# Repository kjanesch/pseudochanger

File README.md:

pseudochanger
=============
A project that aims to add an auxiliary input to head units that use the Panasonic variant of the Alpine MBus protocol.

Alpine MBus is a bidirectional one-wire serial interface used for communication between audio head units and peripherals like CD players, CD changers, and tape decks. A period for each bit is 3 ms, and low/high bits are indicated by how long the line is held low. Low for the first 600us indicates a 1, low for 1800 us indicates a 0. Data is a multiple of four bits, and a four-bit check follows the packet, an XOR of all the other 4-bit chunks.

The Panasonic variant uses different ping and ACK codes, sends some data at different times, and does what looks like type detection by sending out a cycle of codes. The included library reflects these differences.

This project was developed specifically for the 2002 Subaru WRX head unit, model CQ-EF7260A, and should work with other Panasonic head units that have the same 16-pin connector on the back, as also found in some Mazdas and Hondas.

This project contains:
 - Arduino MBusPanasonic library
   - Timing-driven bus interface
   - Sends static timestamp of Disc 1, Track 1, Time A:0A to indicate aux input 
 - Example implementation (pseudochanger)
   - Uses the Teensy branch of [finsprings/arduinaap](https://github.com/finsprings/arduinaap/tree/teensy) for the iPod Accessory Protocol interface.
 - Circuit and PCB diagrams
   - V1 is the handmade, free-handed version
   - V2 is the (incomplete) PCB of V1 with minor tweaks
   - V2.5 is a completely respun, integrated design
     - Built-in Atmega 32U4 (or 16U4 depending on code space needs)
     - Onboard switching regulator to generate 5V supply from +12V and accessory on/off
     - Smaller (0805/0603) SMT components
     - Ethernet jack for iPod connector
     - Op-amp based switch to make it solid state

TODO: 
 - Library:
   - Interrupt-driven approach to receiving and sending MBus data
   - Integrated polling routine to extract button presses
   - Fix issues with generating timestamps
   - Add a short example that doesn't keep state, switch between inputs, or control iPods (fewer I/Os, less setup, smaller code, no dependencies)
 - Implementation: 
   - Sort out why iPod interface doesn't work (Hardware? Software?)
 - EAGLE files:
   - Finish V2.5 PCB and BOM, construct boards IRL and test

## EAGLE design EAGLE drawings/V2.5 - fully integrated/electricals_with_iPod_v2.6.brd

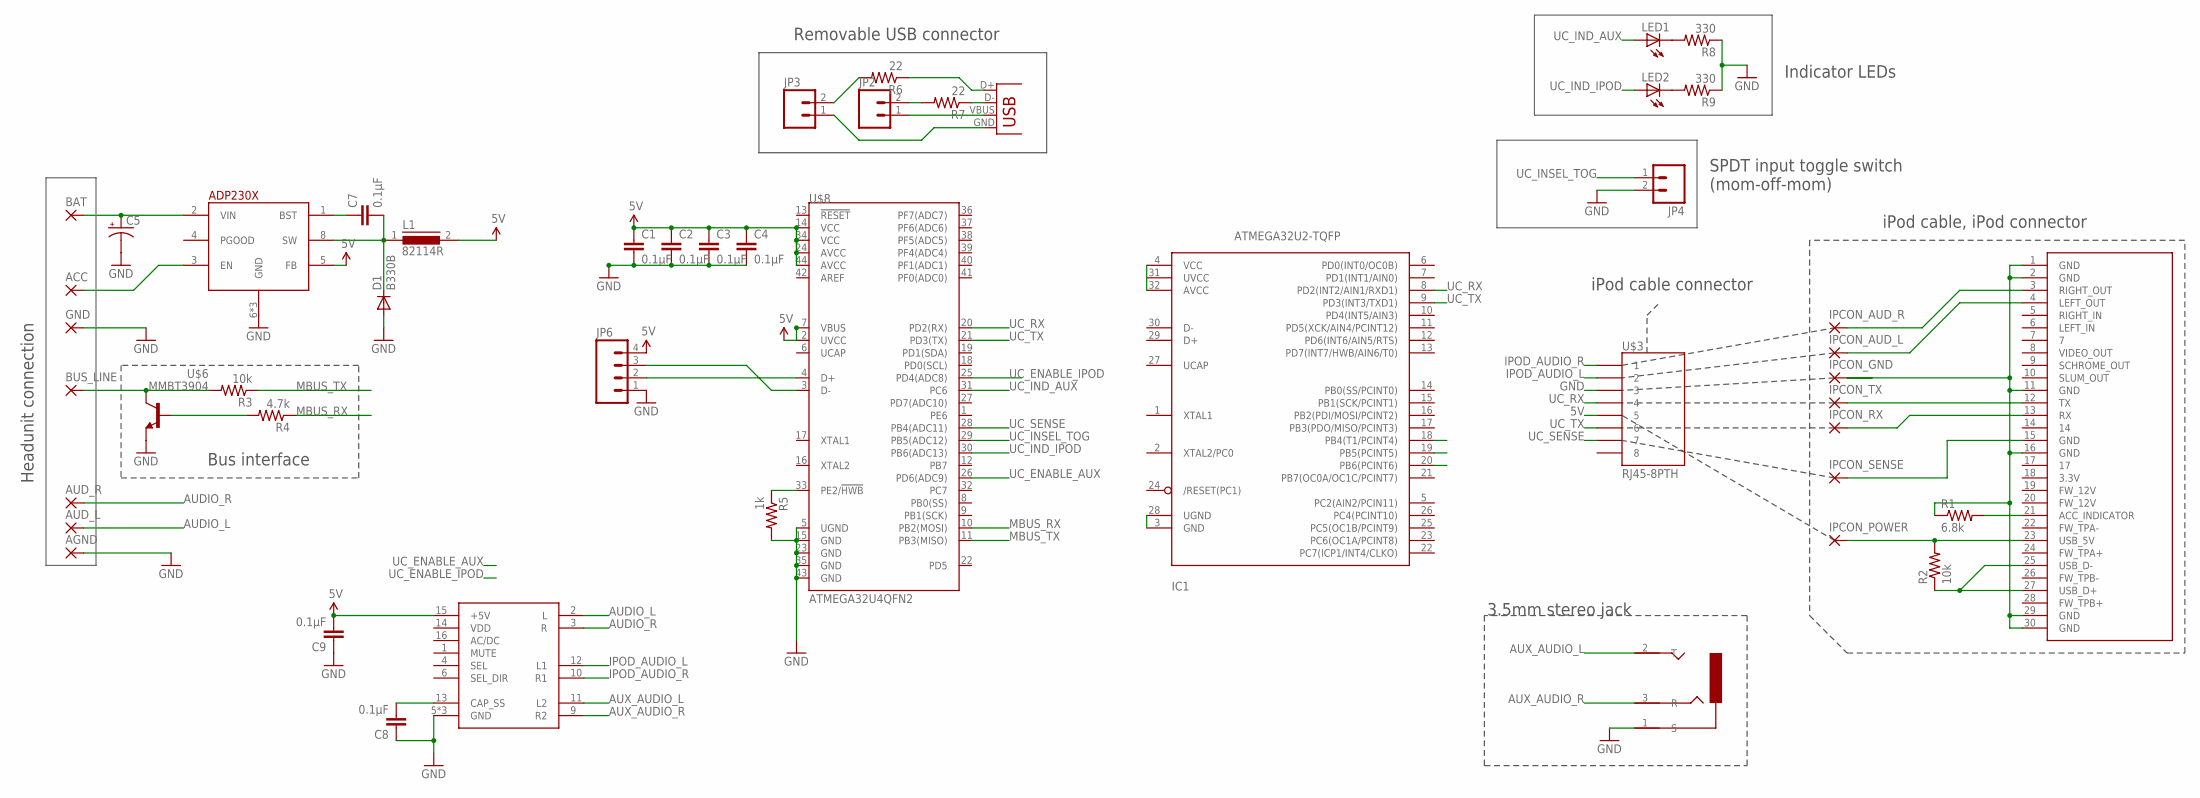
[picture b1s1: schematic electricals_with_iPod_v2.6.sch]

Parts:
ACC: 1,6/0,9
AGND: 1,6/0,9
AUD_L: 1,6/0,9
AUD_R: 1,6/0,9
BAT: 2,54/1,1
BUS_LINE: 1,6/0,9
C1, C2, C3, C4, C7, C8, C9: 0.1µF; 0603-CAP
C5: CAP_POLPTH2; CPOL-RADIAL-10UF-25V
D1: B330B; SMA-DIODE_ALT
GND: 2,54/1,1
IC1: ATMEGA32U2-TQFP; TQFP32-08
IPCON_AUD_L: 1,6/0,9
IPCON_AUD_R: 1,6/0,9
IPCON_GND: 1,6/0,9
IPCON_POWER: 1,6/0,9
IPCON_RX: 1,6/0,9
IPCON_SENSE: 1,6/0,9
IPCON_TX: 1,6/0,9
JP1: USBSMD; USB-MINIB
JP2, JP3: M02POGO_PIN_HOLES_ONLY; 1X02_PP_HOLES_ONLY
JP4: M02LOCK; 1X02_LOCK
JP6: M04PTH; 1X04
L1: 82114R
LED1, LED2: LED0603; LED-0603
R1: 6.8k; 0603-RES
R2, R3: 10k; 0603-RES
R4: 4.7k; 0603-RES
R5: 1k; 0603-RES
R6, R7: 22; 0603-RES
R8, R9: 330; 0603-RES
U$1: IPOD_CONNECTOR_MALE; IPOD_MALE_CONNECTOR
U$3: RJ45-8PTH; RJ45-8
U$5: ADP230X; SO8-THERM
U$6: MMBT3904; SOT23-3
U$7: STEREO_JACK_SJ1-353XNG3NG; 3.5MM_SJ1-353XNG
U$8: ATMEGA32U4QFN2; SPARKFUN-DIGITALIC_QFN-44-NOPAD
U$11: ISL54405IRTZ; QFN-16

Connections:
5V: C1.1, C2.1, C3.1, C4.1, C9.2, JP6.4, L1.2, U$3.5, U$5.5 (FB), U$8.2 (UVCC), U$8.7 (VBUS), U$8.14 (VCC), U$8.24 (AVCC), U$8.34 (VCC), U$8.44 (AVCC), U$11.15 (+5V)
AUDIO_L: AUD_L.1, U$11.2 (L)
AUDIO_R: AUD_R.1, U$11.3 (R)
AUX_AUDIO_L: U$7.2 (T), U$11.11 (L2)
AUX_AUDIO_R: U$7.3 (R), U$11.9 (R2)
GND: AGND.1, C1.2, C2.2, C3.2, C4.2, C5.2 (-), C8.1, C9.1, D1.A, GND.1, JP4.2, JP6.1, R5.2, R8.1, R9.1, U$3.3, U$5.6 (GND), U$5.7 (GND), U$5.PAD (GND), U$6.2 (E), U$7.1 (S), U$8.5 (UGND), U$8.15 (GND), U$8.23 (GND), U$8.35 (GND), U$8.43 (GND), U$11.5 (GND), U$11.7 (GND), U$11.8 (GND)
IPOD_AUDIO_L: U$3.2, U$11.12 (L1)
IPOD_AUDIO_R: U$3.1, U$11.10 (R1)
IP_GND: IPCON_GND.1, R1.1, U$1.1 (GND), U$1.2 (GND), U$1.11 (GND), U$1.16 (GND), U$1.29 (GND), U$1.30 (GND)
MBUS_RX: R4.1, U$8.10 (PB2(MOSI))
MBUS_TX: R3.1, U$8.11 (PB3(MISO))
unnamed: ACC.1, U$5.3 (EN)
unnamed: BAT.1, C5.1 (+), U$5.2 (VIN)
unnamed: C7.2, D1.C, L1.1, U$5.8 (SW)
unnamed: IPCON_POWER.1, R2.2, U$1.23 (USB_5V)
unnamed: C7.1, U$5.1 (BST)
unnamed: IPCON_SENSE.1, U$1.15 (GND)
unnamed: IPCON_RX.1, U$1.13 (RX)
unnamed: IPCON_TX.1, U$1.12 (TX)
unnamed: IPCON_AUD_R.1, U$1.3 (RIGHT_OUT)
unnamed: IPCON_AUD_L.1, U$1.4 (LEFT_OUT)
unnamed: R2.1, U$1.25 (USB_D-), U$1.27 (USB_D+)
unnamed: C8.2, U$11.13 (CAP_SS)
unnamed: R1.2, U$1.21 (ACC_INDICATOR)
unnamed: R5.1, U$8.33 (PE2/!HWB)
unnamed: LED1.C, R8.2
unnamed: LED2.C, R9.2
unnamed: IC1.3 (GND), IC1.28 (UGND)
unnamed: IC1.4 (VCC), IC1.32 (AVCC)
unnamed: BUS_LINE.1, R3.2, U$6.3 (C)
unnamed: R4.2, U$6.1 (B)
unnamed: JP1.D+, R6.1
unnamed: JP1.D-, R7.1
UC_ENABLE_AUX: U$8.26 (PD6(ADC9))
UC_ENABLE_IPOD: U$8.25 (PD4(ADC8))
UC_IND_AUX: LED1.A, U$8.31 (PC6)
UC_IND_IPOD: LED2.A, U$8.30 (PB6(ADC13))
UC_INSEL_TOG: JP4.1, U$8.29 (PB5(ADC12))
UC_RX: IC1.8 (PD2(INT2/AIN1/RXD1)), U$3.4, U$8.20 (PD2(RX))
UC_SENSE: U$3.7, U$8.28 (PB4(ADC11))
UC_TX: IC1.9 (PD3(INT3/TXD1)), U$3.6, U$8.21 (PD3(TX))
USB_BOB_D+: JP3.2, R6.2
USB_BOB_D-: JP2.2, R7.2
USB_BOB_GND: JP1.GND, JP3.1
USB_BOB_VBUS: JP1.VBUS, JP2.1
USB_D+: JP6.2, U$8.4 (D+)
USB_D-: JP6.3, U$8.3 (D-)

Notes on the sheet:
Bus interface
SPDT input toggle switch (mom-off-mom)
3.5mm stereo jack
Indicator LEDs
iPod cable, iPod connector
iPod cable connector
Headunit connection
Removable USB connector

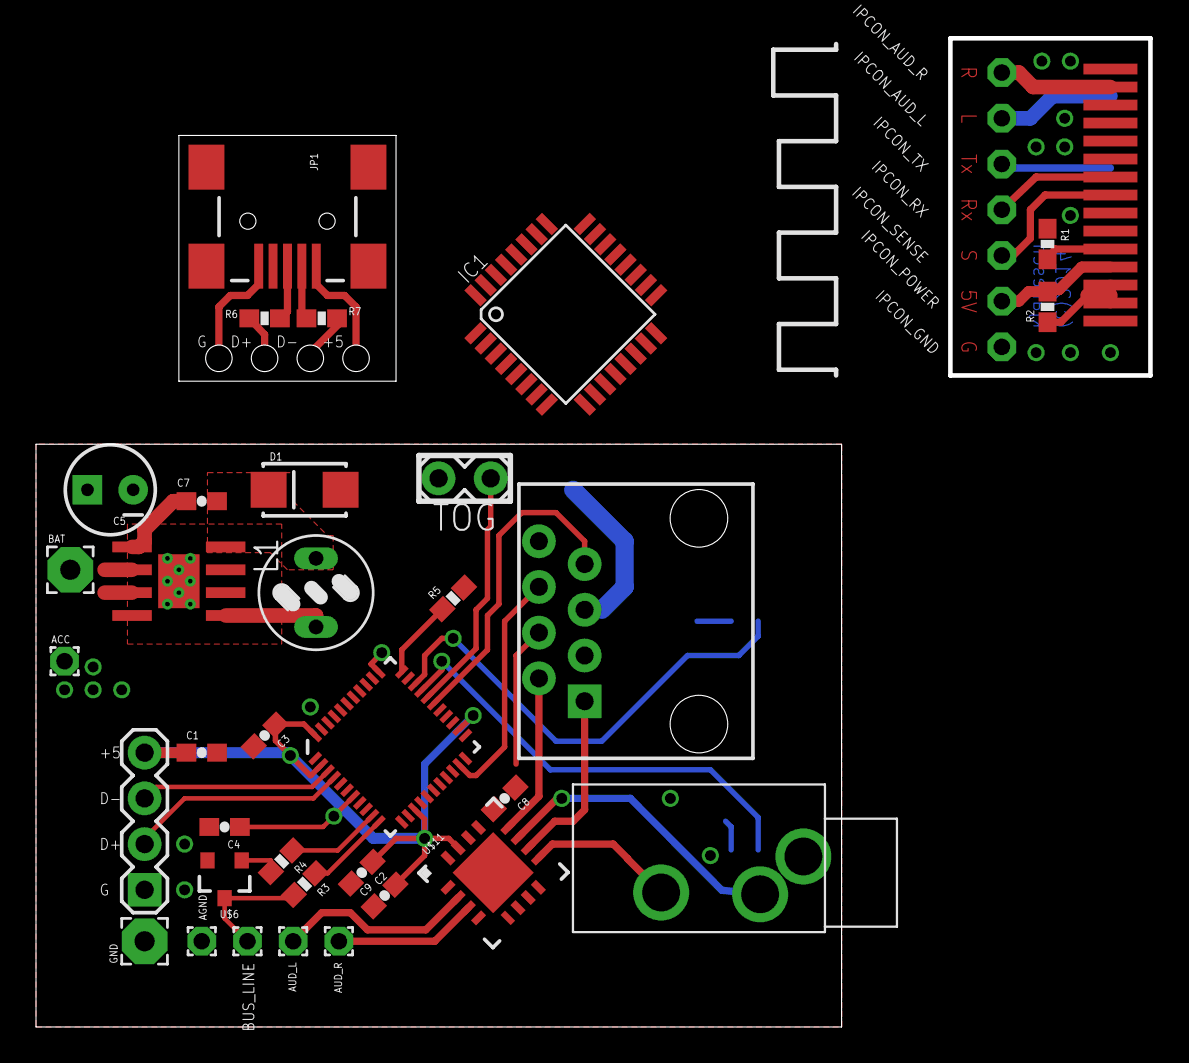
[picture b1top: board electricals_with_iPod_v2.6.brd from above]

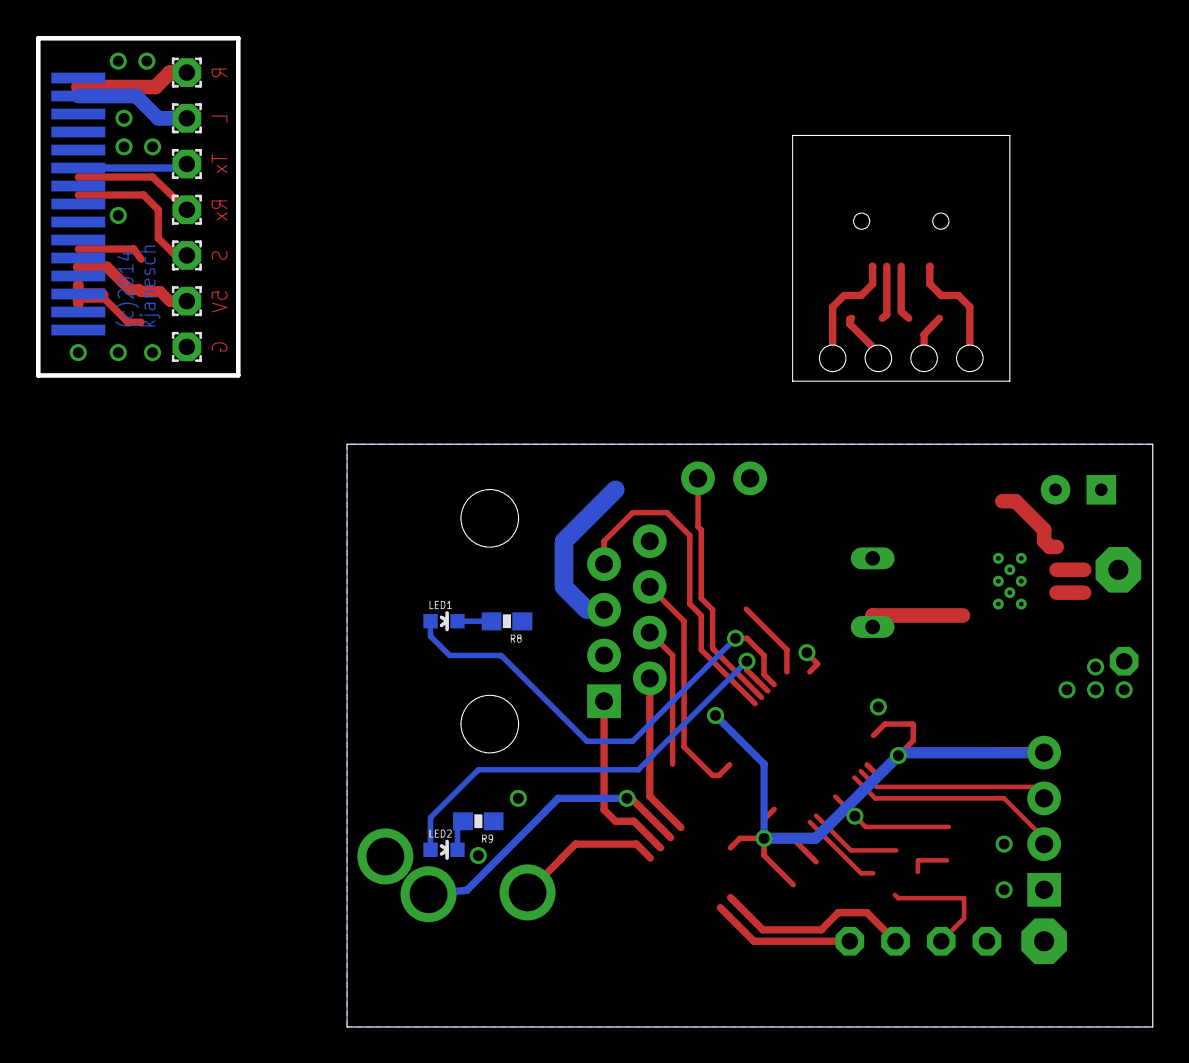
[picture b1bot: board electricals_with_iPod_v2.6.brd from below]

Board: 2 copper layers, 61.9 x 54.9 mm, 48 parts (12 on the bottom side), 45 nets.

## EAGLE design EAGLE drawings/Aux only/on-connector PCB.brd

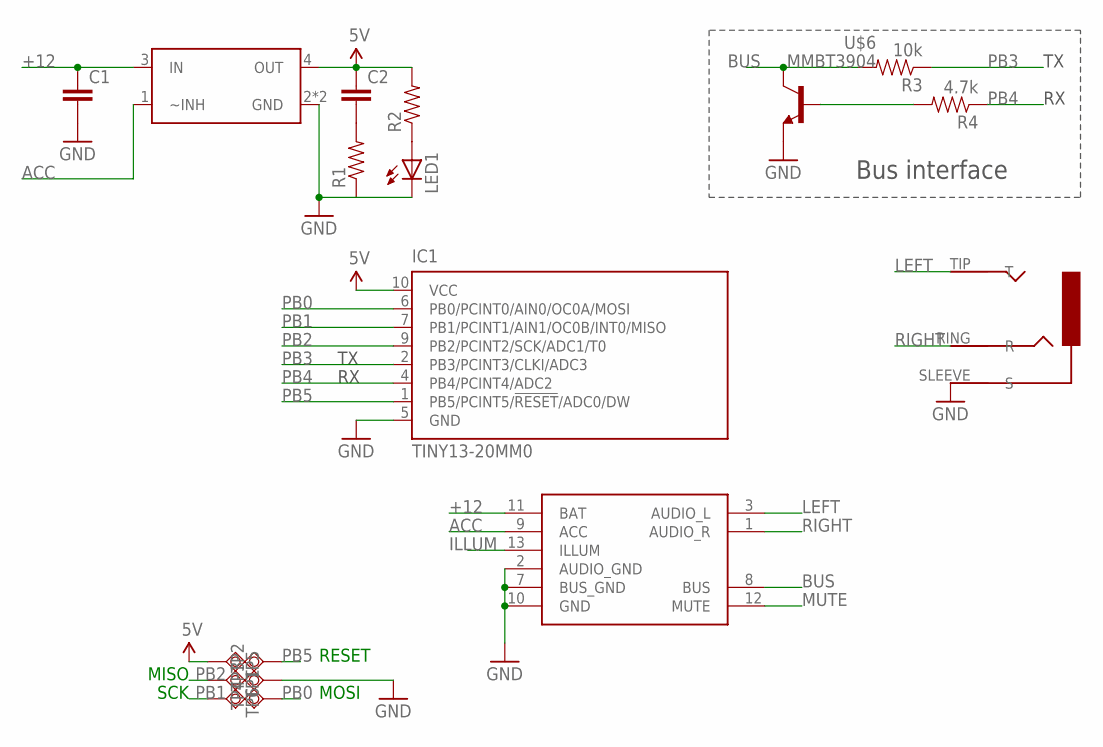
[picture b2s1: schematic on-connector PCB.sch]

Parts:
C1, C2: CAP0603-CAP; 0603-CAP
IC1: TINY13-20MM0; 10M1
LED1: LED0603; LED-0603
R1, R2: RESISTOR0603-RES; 0603-RES
R3: 10k; 0805
R4: 4.7k; 0805
TP1, TP2, TP3, TP4, TP6: TPSQTP07R; TP07R
TP5: TPSQTP07SQ; TP07SQ
U$1: PANASONIC_CN702_BACKBOARD; 040_MLCII_BACK_CN702
U$2: STEREO_JACK_SJ_352X; AUDIO-JACK-3.5MM-SMD
U$6: MMBT3904; SOT23-3
U$7: IFX20001; PG-SCT595-5

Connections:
5V: C2.1, IC1.10 (VCC), R2.2, TP5.TP, U$7.4 (OUT)
+12: C1.1, U$1.11 (BAT), U$7.3 (IN)
ACC: U$1.9 (ACC), U$7.1 (~INH)
BUS: R3.2, U$1.8 (BUS), U$6.3 (C)
GND: C1.2, IC1.5 (GND), IC1.11 (GND), LED1.C, R1.1, TP3.TP, U$1.2 (AUDIO_GND), U$1.7 (BUS_GND), U$1.10 (GND), U$2.SLEEVE (S), U$6.2 (E), U$7.2 (GND), U$7.5 (GND)
ILLUM: U$1.13 (ILLUM)
LEFT: U$1.3 (AUDIO_L), U$2.TIP (T)
MUTE: U$1.12 (MUTE)
unnamed: C2.2, R1.2
unnamed: LED1.A, R2.1
unnamed: R4.2, U$6.1 (B)
PB0: IC1.6 (PB0/PCINT0/AIN0/OC0A/MOSI), TP4.TP
PB1: IC1.7 (PB1/PCINT1/AIN1/OC0B/INT0/MISO), TP6.TP
PB2: IC1.9 (PB2/PCINT2/SCK/ADC1/T0), TP1.TP
PB3: IC1.2 (PB3/PCINT3/CLKI/ADC3), R3.1
PB4: IC1.4 (PB4/PCINT4/ADC2), R4.1
PB5: IC1.1 (PB5/PCINT5/!RESET!/ADC0/DW), TP2.TP
RIGHT: U$1.1 (AUDIO_R), U$2.RING (R)

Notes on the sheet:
Bus interface
MOSI
MISO
SCK
RESET

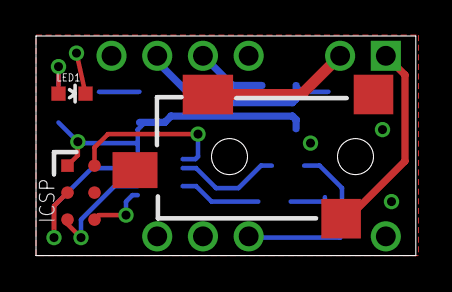
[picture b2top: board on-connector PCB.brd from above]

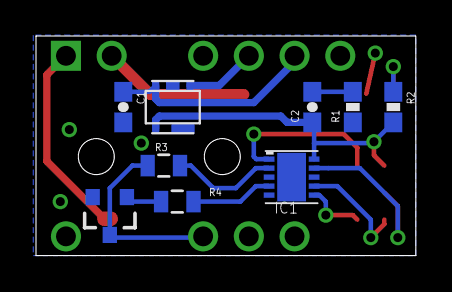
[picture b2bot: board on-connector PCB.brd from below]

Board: 2 copper layers, 21.1 x 12.2 mm, 18 parts (9 on the bottom side), 16 nets.

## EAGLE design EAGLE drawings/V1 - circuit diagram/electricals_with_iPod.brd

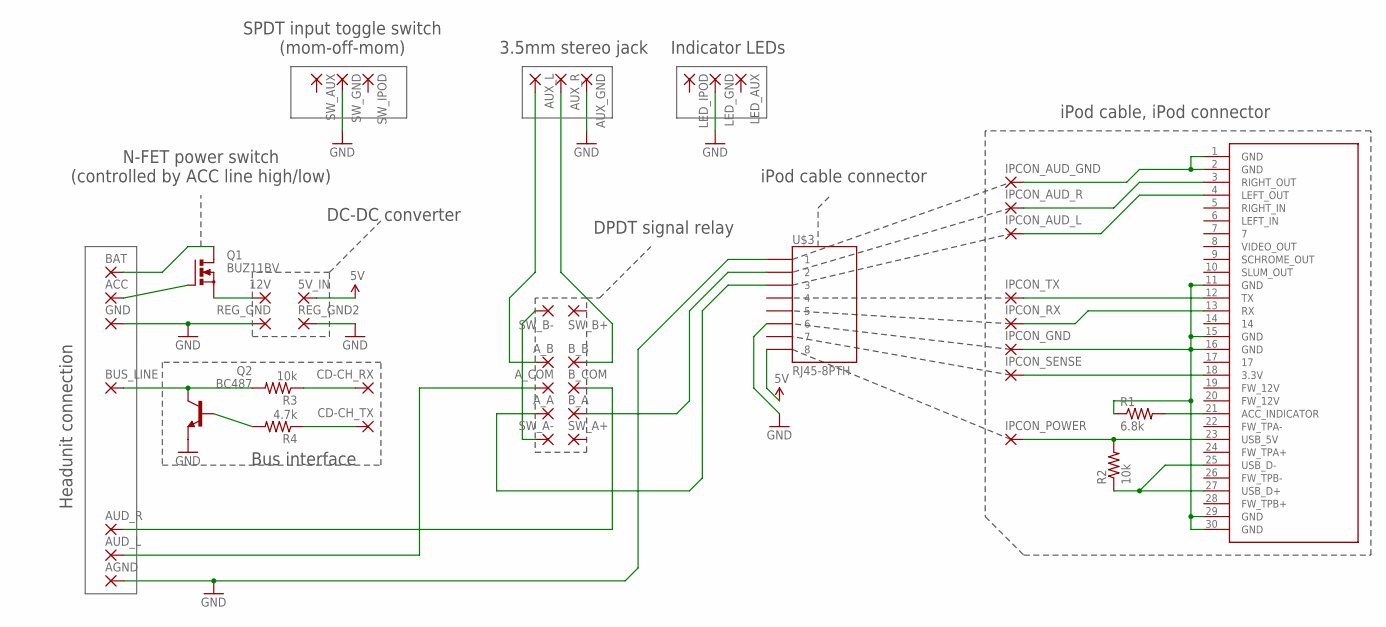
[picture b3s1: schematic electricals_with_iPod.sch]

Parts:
5V_IN, 12V: 2,54/1,1
ACC: 1,6/0,9
AGND: 1,6/0,9
AUD_L: 1,6/0,9
AUD_R: 1,6/0,9
AUX_GND: 1,6/0,9
AUX_L: 1,6/0,9
AUX_R: 1,6/0,9
A_A: 1,6/0,9
A_B: 1,6/0,9
A_COM: 1,6/0,9
BAT: 2,54/1,1
BUS_LINE: 1,6/0,9
B_A: 1,6/0,9
B_B: 1,6/0,9
B_COM: 1,6/0,9
CD-CH_RX: 1,6/0,9
CD-CH_TX: 1,6/0,9
GND: 2,54/1,1
IPCON_AUD_GND: 1,6/0,9
IPCON_AUD_L: 1,6/0,9
IPCON_AUD_R: 1,6/0,9
IPCON_GND: 1,6/0,9
IPCON_POWER: 1,6/0,9
IPCON_RX: 1,6/0,9
IPCON_SENSE: 1,6/0,9
IPCON_TX: 1,6/0,9
LED_AUX: 1,6/0,9
LED_GND: 1,6/0,9
LED_IPOD: 1,6/0,9
Q1: BUZ11BV; TO220BV
Q2: BC487; TO92-EBC
R1: 6.8k; 1206
R2, R3: 10k; 1206
R4: 4.7k; 1206
REG_GND, REG_GND2: 2,54/1,1
SW_A+: 1,6/0,9
SW_A-: 1,6/0,9
SW_AUX: 1,6/0,9
SW_B+: 1,6/0,9
SW_B-: 1,6/0,9
SW_GND: 1,6/0,9
SW_IPOD: 1,6/0,9
U$1: IPOD_CONNECTOR_MALE; IPOD_MALE_CONNECTOR
U$3: RJ45-8PTH; RJ45-8

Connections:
5V: 5V_IN.1, U$3.8
GND: AGND.1, AUX_GND.1, GND.1, LED_GND.1, Q2.E, REG_GND.1, REG_GND2.1, SW_GND.1, U$3.1, U$3.6
unnamed: ACC.1, Q1.G
unnamed: BAT.1, Q1.D
unnamed: 12V.1, Q1.S
unnamed: IPCON_POWER.1, R2.2, U$1.23 (USB_5V)
unnamed: IPCON_AUD_GND.1, U$1.1 (GND), U$1.2 (GND)
unnamed: IPCON_SENSE.1, U$1.18 (3.3V)
unnamed: IPCON_RX.1, U$1.13 (RX)
unnamed: IPCON_TX.1, U$1.12 (TX)
unnamed: IPCON_AUD_R.1, U$1.3 (RIGHT_OUT)
unnamed: IPCON_AUD_L.1, U$1.4 (LEFT_OUT)
unnamed: R2.1, U$1.25 (USB_D-), U$1.27 (USB_D+)
unnamed: IPCON_GND.1, R1.1, U$1.11 (GND), U$1.15 (GND), U$1.16 (GND), U$1.29 (GND), U$1.30 (GND)
unnamed: R1.2, U$1.21 (ACC_INDICATOR)
unnamed: SW_A-.1, SW_B-.1
unnamed: AUD_L.1, A_COM.1
unnamed: AUD_R.1, B_COM.1
unnamed: AUX_L.1, A_B.1
unnamed: AUX_R.1, B_B.1
unnamed: BUS_LINE.1, Q2.C, R3.2
unnamed: Q2.B, R4.2
unnamed: CD-CH_RX.1, R3.1
unnamed: CD-CH_TX.1, R4.1
unnamed: B_A.1, U$3.2
unnamed: A_A.1, U$3.3

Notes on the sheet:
Bus interface
N-FET power switch (controlled by ACC line high/low)
DC-DC converter
SPDT input toggle switch (mom-off-mom)
3.5mm stereo jack
Indicator LEDs
iPod cable, iPod connector
iPod cable connector
DPDT signal relay
Headunit connection

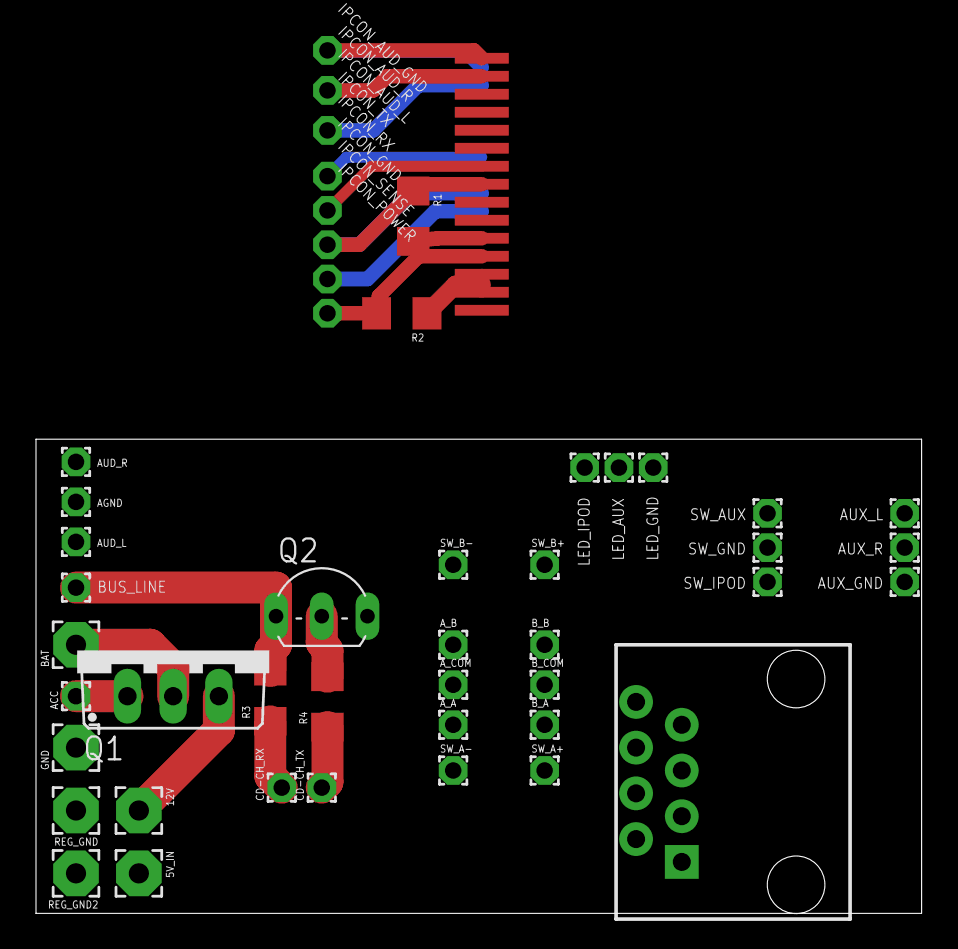
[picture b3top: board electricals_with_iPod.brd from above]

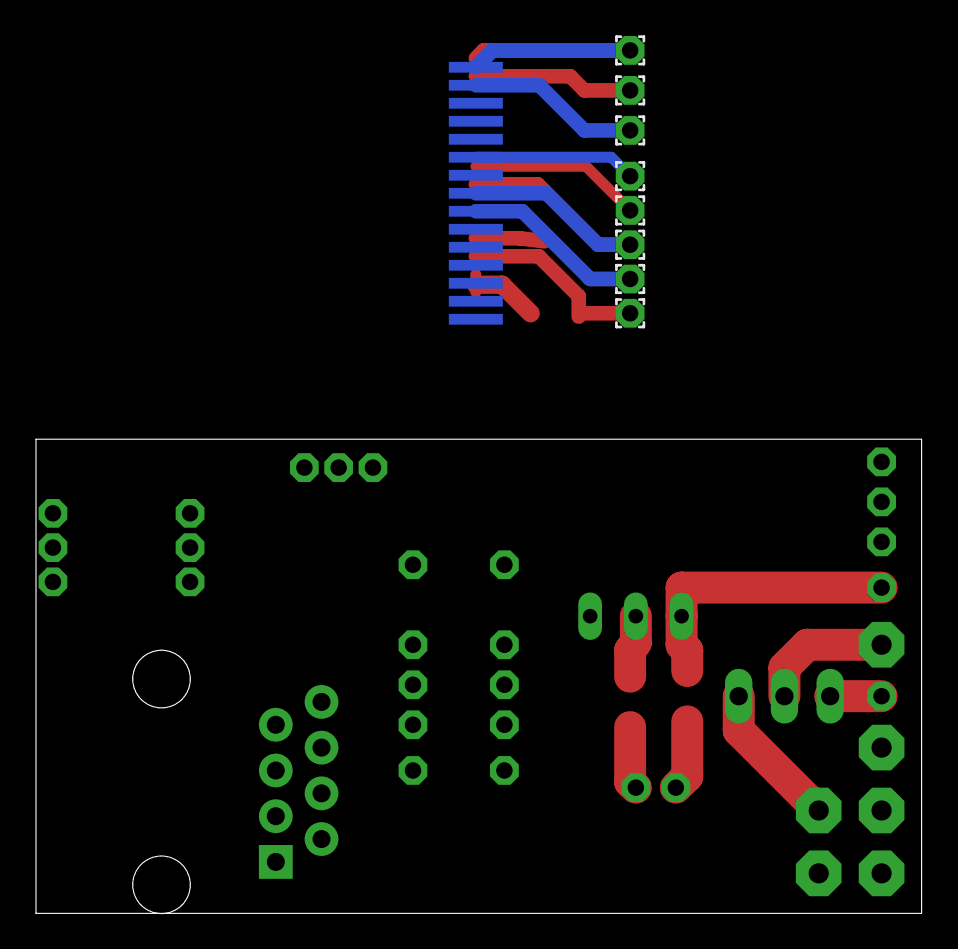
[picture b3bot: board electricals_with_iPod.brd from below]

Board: 2 copper layers, 49.2 x 26.3 mm, 48 parts (9 on the bottom side), 26 nets.

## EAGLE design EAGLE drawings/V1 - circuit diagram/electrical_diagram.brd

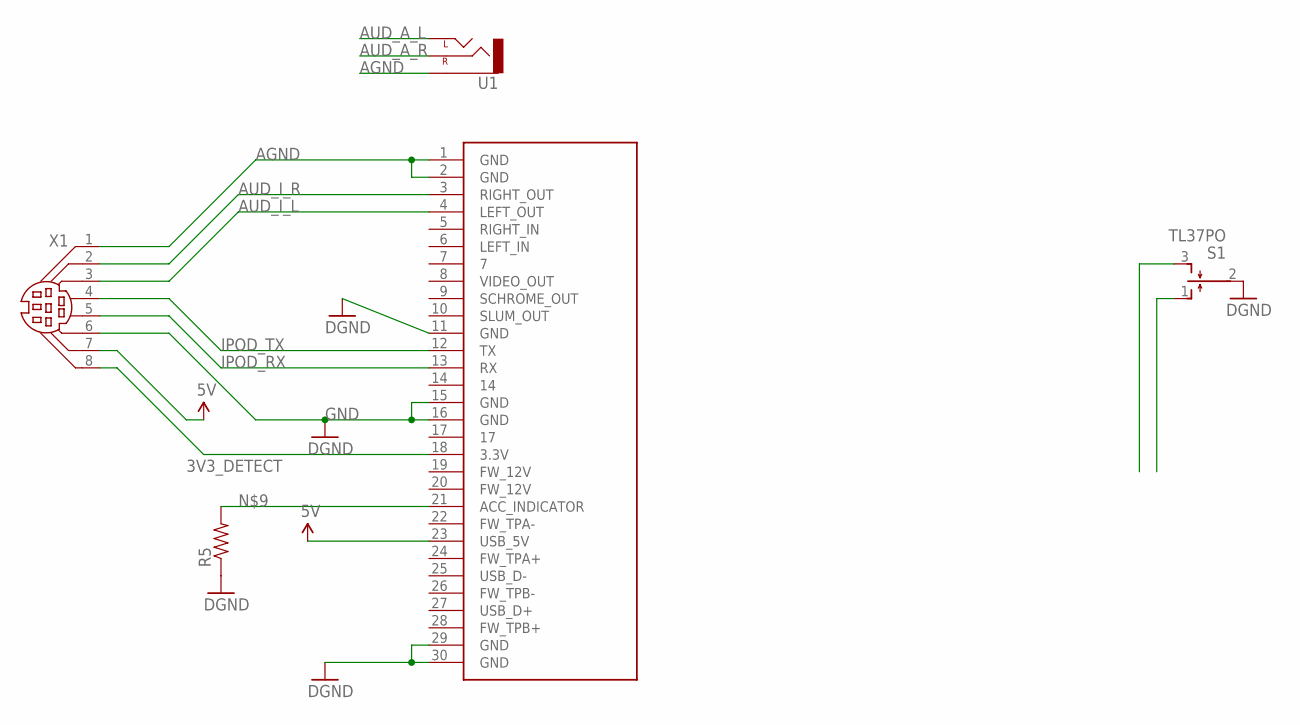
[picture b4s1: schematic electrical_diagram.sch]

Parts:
R5: RESISTOR0805-RES; 0805
S1: TL37PO; TL3XPO
U1: AUDIO-JACKSMD2; AUDIO-JACK-3.5MM-SMD
U$1: IPOD_CONNECTOR_MALE; IPOD_MALE_CONNECTOR
X1: MDIN08K

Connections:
3V3_DETECT: U$1.18 (3.3V), X1.8
5V: U$1.23 (USB_5V), X1.7
AGND: U1.SLEEVE, U$1.1 (GND), U$1.2 (GND), X1.1
AUD_A_L: U1.TIP (LEFT)
AUD_A_R: U1.RING (RIGHT)
AUD_I_L: U$1.4 (LEFT_OUT), X1.3
AUD_I_R: U$1.3 (RIGHT_OUT), X1.2
GND: R5.1, S1.2, U$1.11 (GND), U$1.15 (GND), U$1.16 (GND), U$1.29 (GND), U$1.30 (GND), X1.6
IPOD_RX: U$1.13 (RX), X1.5
IPOD_TX: U$1.12 (TX), X1.4
unnamed: R5.2, U$1.21 (ACC_INDICATOR)

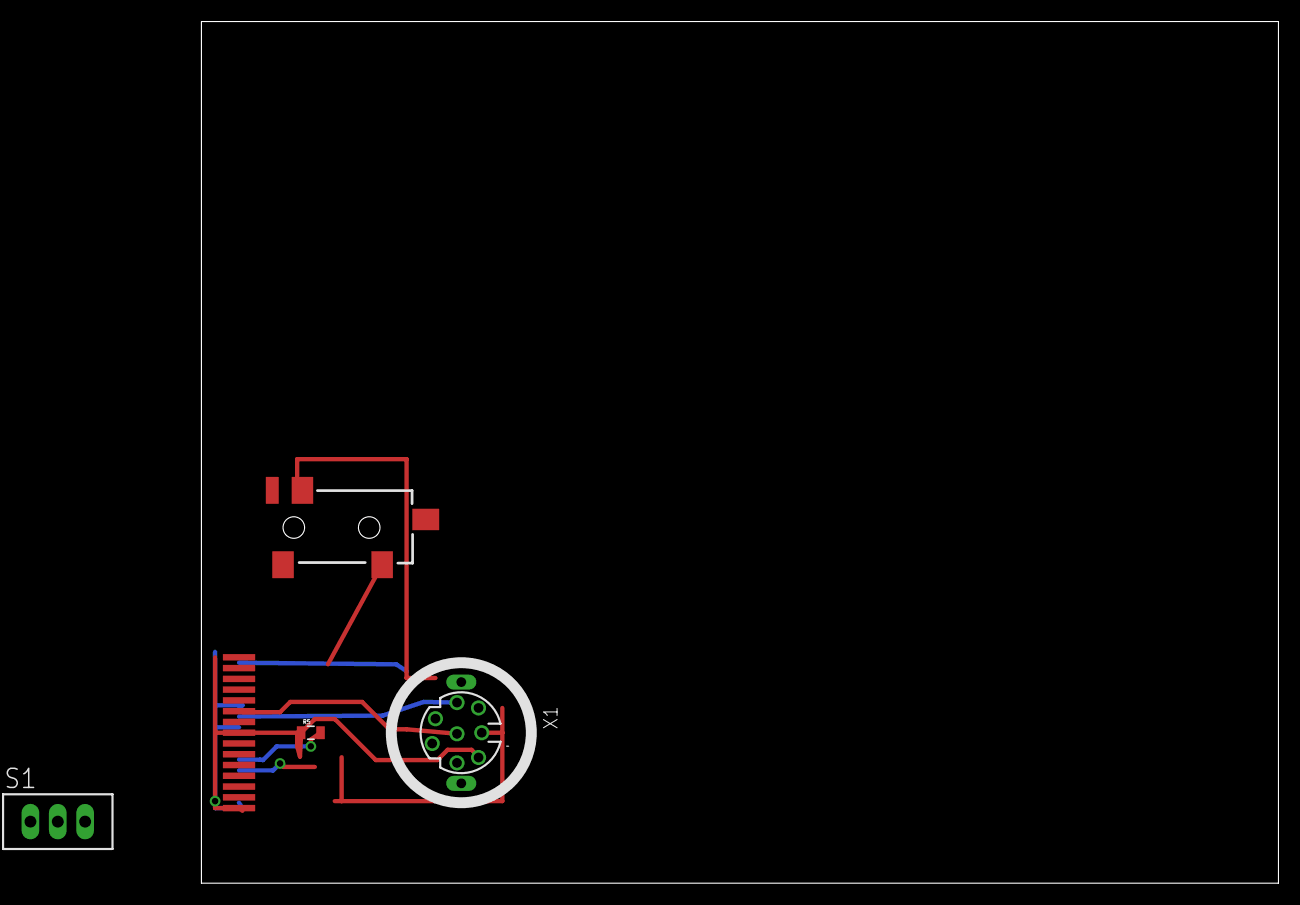
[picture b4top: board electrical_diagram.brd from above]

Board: 2 copper layers, 100.0 x 80.0 mm, 5 parts (0 on the bottom side), 9 nets.

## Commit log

2013-08-14 initital commit, working basic aux-in.
    ipod controls still not working; may be wiring.
2013-11-17 Updated the readme so that it's actually accurate :/
2014-06-24 Added optional debugging, tweaked iPod interface
    DEBUG_MODE flag toggles Serial print statements
    tweaks made to AdvancedRemote callbacks for better clarity in variables
    iPod interface still not working, likely a hardware problem.
2014-07-21 reorganized project
    added EAGLE board files
    updated keywords.txt
    split off Arduino library from project
    reorganized defines
2014-07-21 Fixed missing include
2014-09-26 Added v2.6 - smaller, 0603 passives, QFN mega*U4
    Files edited with EAGLE 7.1.0
    Split off v2.6
    - board about .25” shorter
    - 0603 passives
    - QFN package ATMega*U4
    - rearranged power supply
2014-12-06 iPod breakout split from v2.6, new single-input board
    The iPod connector board was pulled from V2.6 to send to OSHPark
    v2.6 is pending revisions down from the ATMega 16U4 to [8|16|32]U2. May
    shrink more.
    A new board is in the works that can fit on the back of the stereo
    connector, providing only an auxiliary input. Uses an ATTiny.
2015-01-19 Updated aux-only board, preparing to switch to 32/16/8U2

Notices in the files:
EAGLE drawings/V2.5 - fully integrated/electricals_with_iPod_v2.6.brd:
(c)2014
parts and their libraries:
SparkFun-Capacitors: Licensing: CC v3.0 Share-Alike You are welcome to use this library for commercial purposes.
